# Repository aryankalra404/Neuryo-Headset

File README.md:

# Neuryo Headset

Interactive 3D models of the Neuryo EEG + heart-rate headset. Each design is its own model; the start page lists them and lets you switch between them.

**Open it:** https://aryankalra404.github.io/Neuryo-Headset/

| Design | What it is | Direct link |
|---|---|---|
| v1 · 26 Oct design | 4 channels: AF7, AF8, Fz, Pz. TP9 + TP10 linked reference, Fpz ground, saline sponge pods, forehead heart sensor. Has AR and try-on. | https://aryankalra404.github.io/Neuryo-Headset/designs/v1/ |
| v2 · 29 Oct research plan | 6 channels: Fp1, Fp2, Fz, Pz, TP10, eye (VEOG). TP9 reference alone, Fpz bias, hydrogel on the forehead, semi-dry pods in hair, earlobe heart-sensor clip. Built from the Neuryo-Research library (decisions D01 to D28) on the shared realistic head. Superseded by v3. | https://aryankalra404.github.io/Neuryo-Headset/designs/v2/ |
| v3 · 29 Oct review | Superseded by v4. 6 channels on the head (Fp1, Fp2, Fz, Pz, M2, eye) on an 8-channel ADS1299 at gain 12. M1 mastoid-bone reference on SRB2, Fpz bias. One 4 mm snap socket per site with swappable inserts: paste on the forehead, semi-dry pods in hair. **Test kit** toggle adds ECG on channel 7 and dry comparison inserts; **Confidence** colours each part by how sure the plan is. | https://aryankalra404.github.io/Neuryo-Headset/designs/v3/ |
| v4 · 7 Nov product design | Superseded by v6, which keeps its midline band and carriages. Was the launch design (v4.4). A 5-minute in-clinic recording at baseline, day 7 and every visit of a depression treatment course. 7 channels on the head (Fp1, Fp2, Fz, Cz, Pz, M2, eye), M1 reference, Fpz bias. Single-use 3-pad hydrogel forehead strip placed by a nasion template, earlobe heart clip, BMI270, 1000 mAh at the back. Buildable frame for 500–580 mm circumference and 300–390 mm nasion–inion: bought hard-hat ratchet harness with a 3 mm lining or a 7 mm small-head insert; midline band 3D-printed already in the head's curve (PA12, PETG for fit tests) with a TPU tail through a cam lock; spring-loaded semi-dry pods pinned at one size number (1–9) read off a size tape; damp single-use foam tips (2–3 mm proud, set weight) topped up only when the app's wetting check asks; wipe-clean silicone lining. Main board (v4.5): about 70 × 50 mm in the brow module, the analog half copied from the open Low-Cost-EEG board plus a Seeed XIAO ESP32-S3. Page adds a 9-step **Session walkthrough**, head-size and nasion–inion sliders, a buy/print parts list and frame build steps, and a **Single-use vs reusable** overlay. | https://aryankalra404.github.io/Neuryo-Headset/designs/v4/ |
| v5 · arch concept (v5.2) | Superseded by v6. Same electronics and sites as v4.5, new frame: spring arch over Cz, main board in a pod above the left ear and battery above the right, temple arms to soft pads, rear band with a hook under the occiput and a dial. v5.2 (8 Nov): Fz, Cz and Pz in spring carriages on a rigid spine clipped to the arch at Cz, one soft spring per pod. Forehead bare apart from the strip. | https://aryankalra404.github.io/Neuryo-Headset/designs/v5/ |
| v6 · 8 Nov head ring + v4 midline | Superseded by v7 (kept for comparison, as the adjustable-Fz alternative). v4's midline band lying on the head with a spring carriage per pod (one size number 1–9 sets Fz and Pz from Fpz), held between a small front anchor (about 34 × 34 × 7.5 mm, replacing v4's brow module) and a cam lock above the rear dial. Head ring: a front band across the forehead above the strip and v5's rear band with a hook under the occiput and a dial. Board in a pod above the left ear, battery above the right. Real windows in the band and real lead slots in the carriages. v6.1 (9 Nov): the real rev B board from KiCad (77 × 50 mm), pods resized to about 98 × 77 × 22 mm. v6.2 (10 Nov): carriages wrap the rails and click into size notches, rails 3 mm thick beside the windows, Cz pod moved to the test kit (6 channels on the product headset). v6.3 (11 Nov): no Cz in the product or the test kit (decision D36); the band has Fz and Pz windows only, with two lead clips on the solid section between them, and a corrected size table. | https://aryankalra404.github.io/Neuryo-Headset/designs/v6/ |
| v7.2 · 11 Nov simplified ring and fixed Fz | Lead design (proposed; nothing printed or measured). From the 11 Nov design review of v6.3; same montage, electrodes, rev B board and firmware. One continuous printed head ring strap from a pivot behind the left pod, across the forehead and under both pods (a tunnel in each pod's base, 2 × M3); the PN521 nape section kept whole and pivoting on its ends, so the pods carry no ring tension. Chin-strap tabs on the ring (strap in the test kit). Side pods with a flat, chamfered face parallel to the board, 15.5 mm off the skin (was 22), JP1 and TP1 left off; outer box about 107.0 × 69.1 × 25.7 mm, headset 180.4 mm wide (v6.3: 189.1). A clip-in **nasion gauge** sets the midline band's zero; the forehead strip goes on after the headset, from the anchor's pointer. Fz fixed at 69 mm behind the zero (up to 9 mm from its 10-20 site, the same spot every visit); only Pz has a size setting. Tail travel corrected to about 81 mm, pull tab with stretch marks, spare end folded in half under two keepers. v7.1 (same day): fixes from the review of v7, dark grey leads with colour end bands, and a **Midline module** toggle showing the forehead-only configuration (an option, not decided). v7.2 (same day): the hair pod reworked as one printed body with a fill tube and an Ag/AgCl pin standing in the foam, guided in its carriage by two pins that stop it and show the force; print files for the pod in `designs/v7/stl/`. | https://aryankalra404.github.io/Neuryo-Headset/designs/v7/ |
| Ultracortex pod adapter · 8 Nov | Test rig part: holds a Neuryo pod in an OpenBCI Ultracortex Mark IV frame node at Fz, Cz or Pz to test a rigid frame with a spring per pod. Four STL print files plus the generator `tools/uc_adapter.py`. | https://aryankalra404.github.io/Neuryo-Headset/designs/uc-adapter/ |

Add `#v1` to `#v7` to the start page link to open a design straight away.

**Docs:** [docs/](docs/README.md): one file per design ([v1](docs/v1.md), [v2](docs/v2.md), [v3](docs/v3.md), [v4](docs/v4.md), [v5](docs/v5.md), [v6](docs/v6.md), [v7](docs/v7.md), each with why it changed from the one before) and the [shared head](docs/head.md) with all 77 measured 10-10 positions plus the mastoid points M1/M2.

**PCB:** [pcb/](pcb/README.md): rev B in KiCad 10 (77 × 50 mm: Low-Cost-EEG's analog half + a XIAO ESP32-S3, final pin map, ERC/DRC/netlist checks, firmware) and the Low-Cost-EEG reference design it copies (Altium project, Gerbers, schematic, report; GPL-3.0). 5th pass, 11 Nov (every assembled part has an LCSC number, R37 10 k, J1 drill 0.8 mm, JLCPCB placement file, clean order folder, firmware USB-restart fix); 4th pass, 10 Nov (series resistors on SPI, I²C pull-ups, D10 to RESET, test pads, plated XIAO battery holes, bench build). Laid out, waiting for review, not ordered. Rev A (30 Oct, made for v3) is in the git history.

## Adding a new design
1. Copy the latest design folder, for example `designs/v5/` to `designs/v6/`, and change the model in `designs/v6/index.html`. It already loads the shared head from `designs/shared/head/`; pick electrode sites by name (`HEAD.sites.F3`, `HEAD.extra.M1` and so on, see [docs/head.md](docs/head.md)).
2. Add an entry to `designs/designs.json` with its `id`, `name`, `date`, `path`, `channels`, `summary` and `status`.
3. Add `docs/v6.md` with its spec and what changed from v5, and why.

The new design then shows up on the start page and in the switcher.

## Using it on Meta Quest 3S (v1)
1. Open https://aryankalra404.github.io/Neuryo-Headset/designs/v1/ in the **Meta Quest Browser**.
2. Tap **View in AR** and allow the permission prompt.
3. Pinch the headset to lift it off the mannequin, or pinch an electrode pod to pull it out on its own. Pinch empty space to move everything. Reset on the panel puts parts back.
   Right stick: explode. Left stick: turn and resize. Use the floating panel for Inside, Electronics only, Labels and Head.

AR is tested on v1 only. v3 and v4 show a **View in AR** button on headsets that support WebXR, but it has not been tested on the Quest yet. Try-on is v1 only.

## Try it on (webcam or phone)
v7: https://aryankalra404.github.io/Neuryo-Headset/designs/v7/tryon.html (or **Try it on** on the v7 page). v6: https://aryankalra404.github.io/Neuryo-Headset/designs/v6/tryon.html. v1: the link below.

### v1
Open https://aryankalra404.github.io/Neuryo-Headset/tryon.html on a laptop or phone, press **Start camera** and face the camera. The headset locks onto your head at true size. Use Size / Up-down / Forward-back to fit it, **Show head guide** to check the fit, and **Take photo** to save a picture. Face tracking runs in the browser with Google MediaPipe; the video is not uploaded.

## In a normal browser
Rotate and zoom the model, see inside, open the **Electrode build** and **Board guide** walkthroughs, and check sources under **Details → Sources**.

v3 adds a Product / Test kit mode switch, a **Display** menu, **Copy link** (opens exactly what you are looking at), **Measure**, and two new Details tabs: **Build** (parts list, wiring, tests) and **Changes** (what moved since v2 and why). See [docs/v3.md](docs/v3.md#on-the-page).

v4 adds **Fit & finish** (head circumference 500–580 mm and nasion–inion 300–390 mm sliders that give the ratchet setting and lining, the strip height and the band size number 1–9; silicone lining vs the dropped knit idea; lining and shell colours), a **Session walkthrough** under Guides (G), a **Session** tab, **Channel numbers** (N) and a **Single-use vs reusable** overlay (U). See [docs/v4.md](docs/v4.md#on-the-page).

v1 is built from the 26 Oct design doc. v2 is built from the 29 Oct research plan; its module, board layout and battery are carried over from v1. Shapes and sizes neither source gives are marked as model estimates in the page. In v2, **All sites** shows every measured 10-10 position on the head.

## Shared head
`designs/shared/head/` holds the mannequin every design uses (v1 to v7): MakeHuman base mesh (CC0), 540 mm head circumference, sites measured with the 10-20 rules. The scripts in `tools/` rebuild it; see [docs/head.md](docs/head.md).

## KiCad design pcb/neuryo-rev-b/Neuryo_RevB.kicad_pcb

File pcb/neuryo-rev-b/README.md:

# Neuryo rev B (KiCad 10)

The Low-Cost-EEG board (commit `3730d31`) with its ESP32-S3 module side replaced by a Seeed XIAO ESP32-S3, the review changes from `../README.md`, I²C headers for the earlobe MAX30102 and a BMI270, and a 77 × 50 mm outline for the v6 left pod. Battery and switch sit at the right-hand (digital) end. The stack-up is JLCPCB 4-layer 1.6 mm. 4th pass (10 Nov): 330 Ω on SCLK/MOSI/CS, I²C pull-ups, D10 → RESET, test pads, plated XIAO battery holes, bench firmware build. 5th pass (11 Nov): part numbers for everything JLCPCB assembles, R37 10 k, J1 drill 0.8 mm, order folder in [review/order-draft-do-not-order/](review/order-draft-do-not-order/). **Not ordered; waiting for review.**

| Path | What it is |
|---|---|
| `Neuryo_RevB.kicad_pro` / `.kicad_sch` / `.kicad_pcb` / `.kicad_dru` | The rev B project (KiCad 10.0.8). Zones are filled. |
| `Neuryo_RevB.pretty`, `Neuryo_RevB.kicad_sym` | New footprints and symbols: Seeed XIAO-ESP32-S3-SMD (from Seeed's library), KiCad's SOT-23 and SW_SPDT_PCM12 (C&K PCM12 slide switch), 1×4 header, 2N7002, PWR_FLAG |
| `Low_Cost_EEG-import-fps.pretty` | Footprints imported from the reference |
| [CHANGES.md](CHANGES.md) | Every change, why, its source, and whether it is verified |
| [REVIEW-CHECKLIST.md](REVIEW-CHECKLIST.md) | What to check before ordering |
| [ASSEMBLY.md](ASSEMBLY.md) | Hand-soldered parts (XIAO through its battery holes), bench board, battery polarity, electrodes |
| [firmware/](firmware/) | Rev B firmware (PlatformIO, XIAO ESP32-S3): upstream's with rev B pins, SRB2, command-driven RESET/START, USB interlock, battery and I²C status |
| `baseline-import/` | The reference imported into KiCad unchanged (plus the translated Altium clearance rules), for side-by-side comparison |
| `review/` | Renders (`top.png`, `bottom.png`), `schematic.pdf`, `layers.pdf`, ERC/DRC JSON, netlists, the netlist and copper diffs, the baseline's reports, a draft fab set (not for ordering) and `bom-jlc.csv`, the BOM with part numbers to order from |
| `scripts/` | The scripts that made every edit: `edit_sch.py`, `edit_pcb.py`, `edit_pcb2.py`, `silkplace.py` (reference-designator placement), `convmod.py` (KiCad 5 footprint to current format), `edit_sch_mpn.py` (restores the reference's part numbers), `jlcbom.py` (BOM with part numbers, no KiCad needed), `edit_sch4.py` and `edit_pcb4.py` (4th pass, one letter per plan step), `edit_sch5.py` and `edit_pcb5.py` (5th pass), `jlcbom.py` / `jlccpl.py` (BOM and placement file), plus the checks (`netdiff.py`, `copperdiff.py`, `drcsum.py`, `gerbdiff.py`) and `runner.sh`, which runs `kicad-cli` and PlatformIO. The paths inside them are the build machine's. |

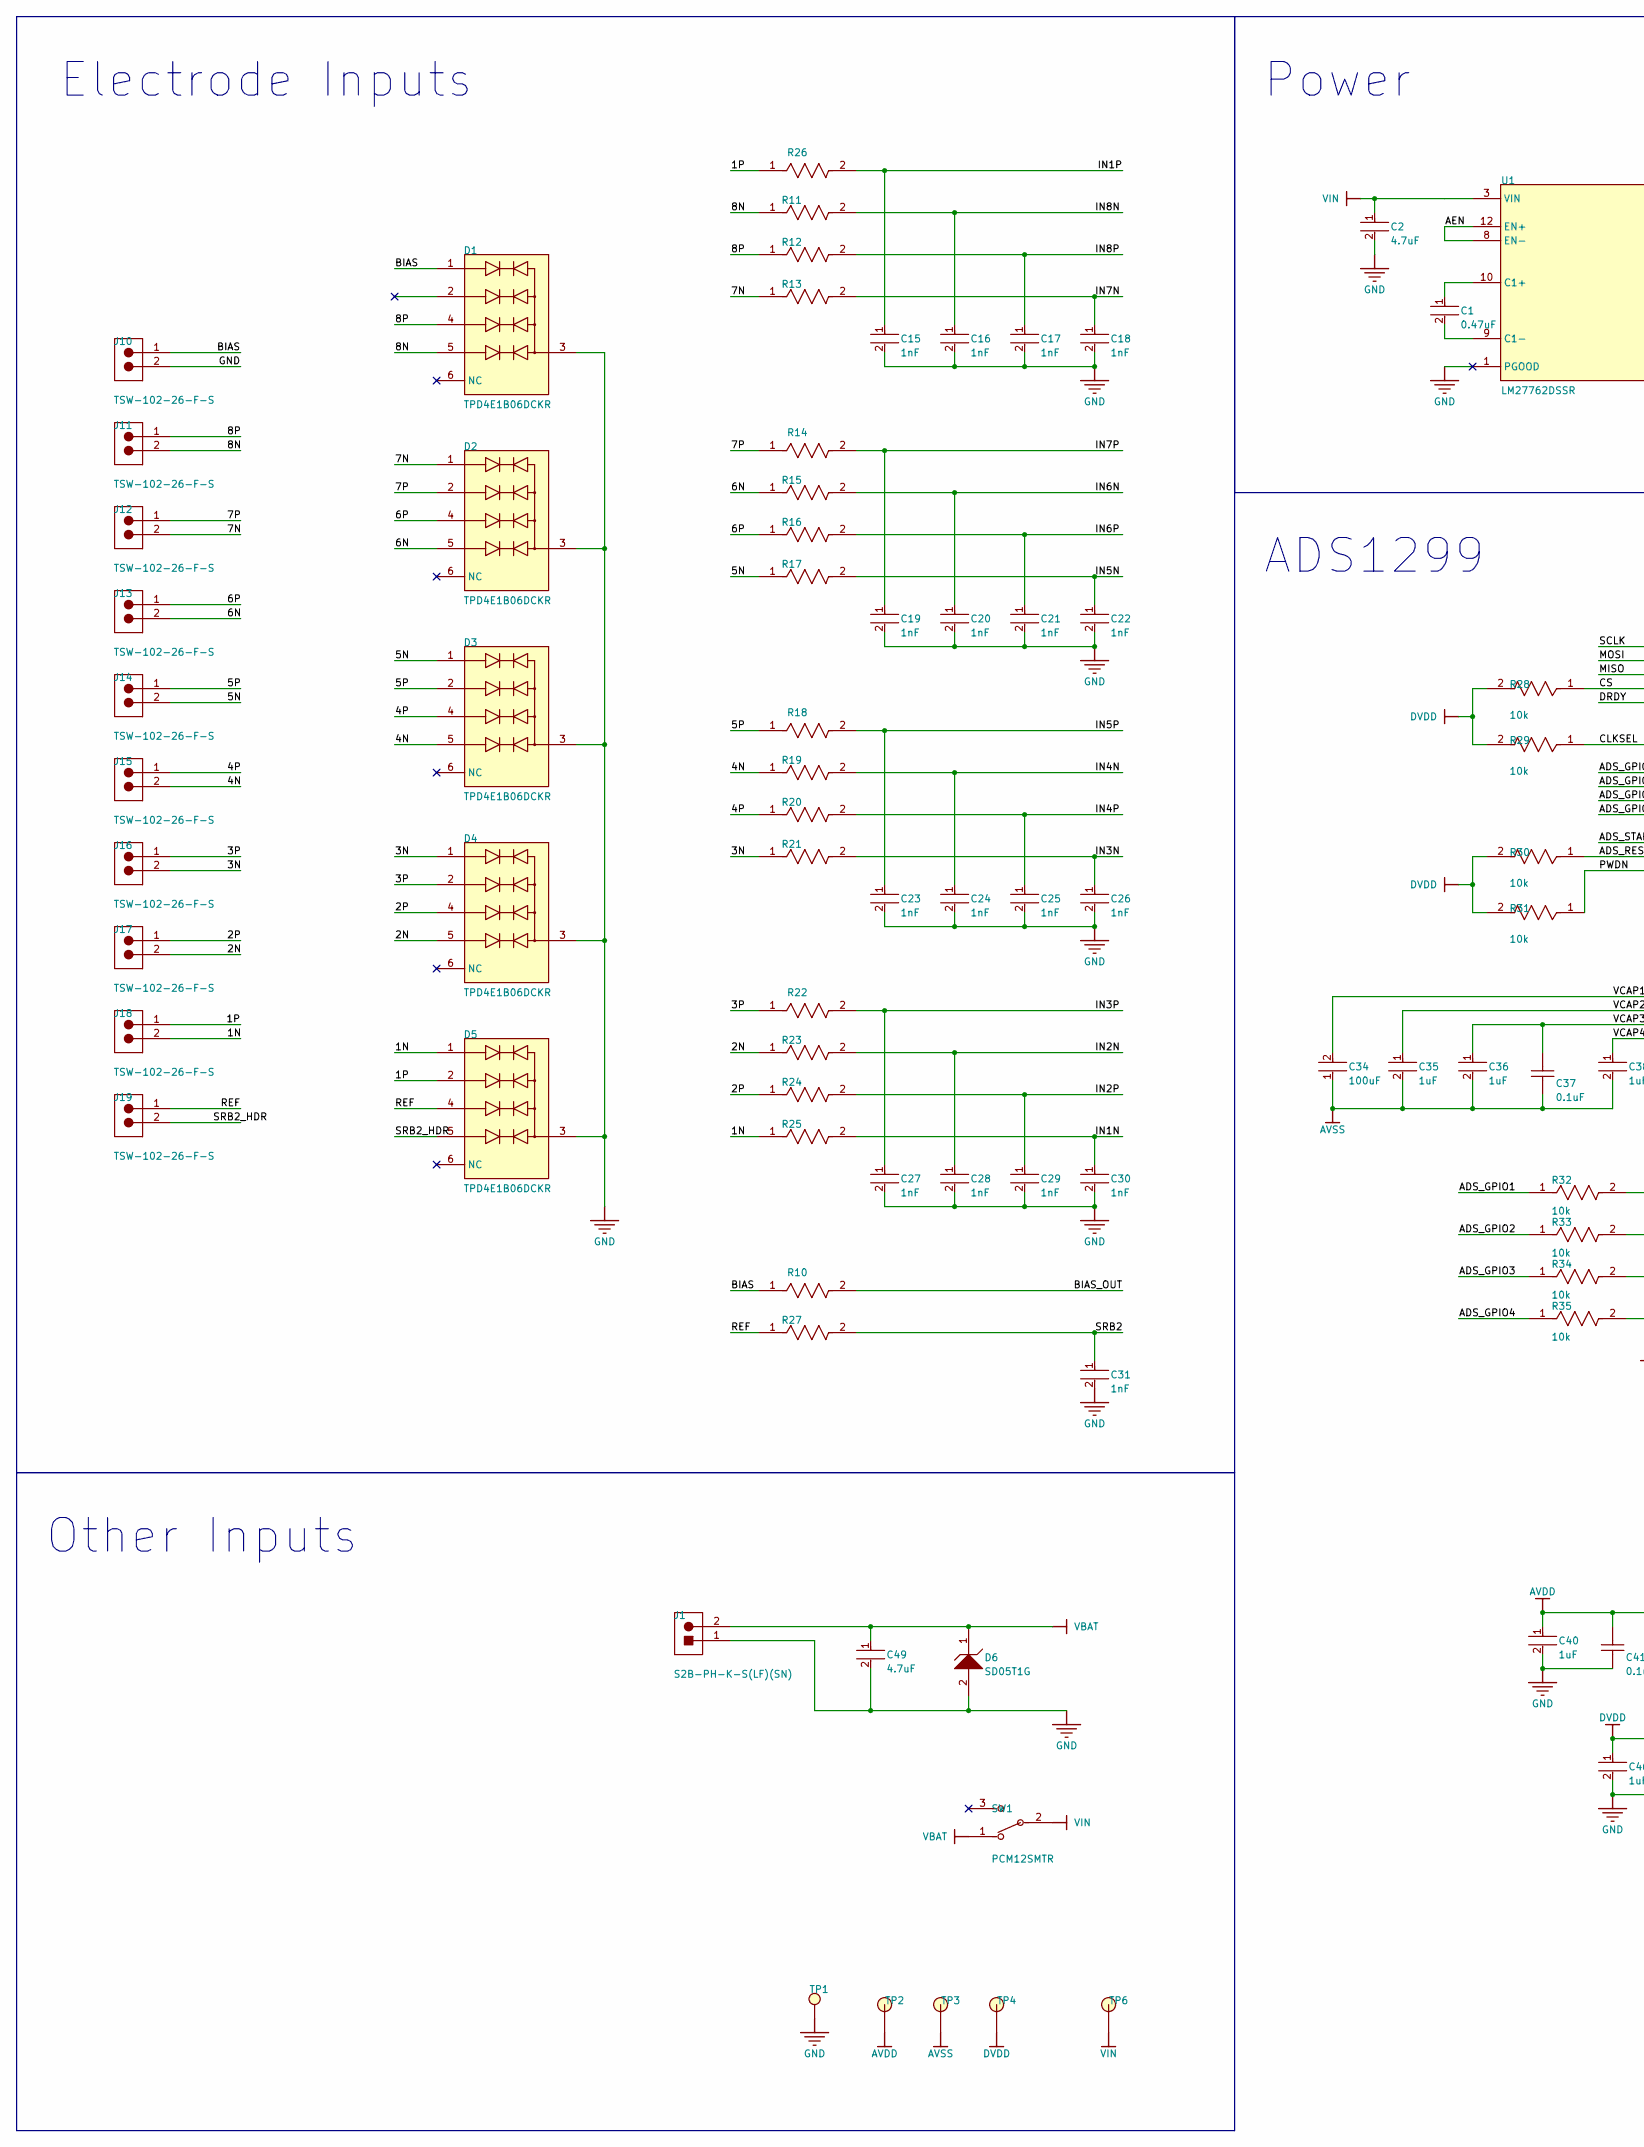
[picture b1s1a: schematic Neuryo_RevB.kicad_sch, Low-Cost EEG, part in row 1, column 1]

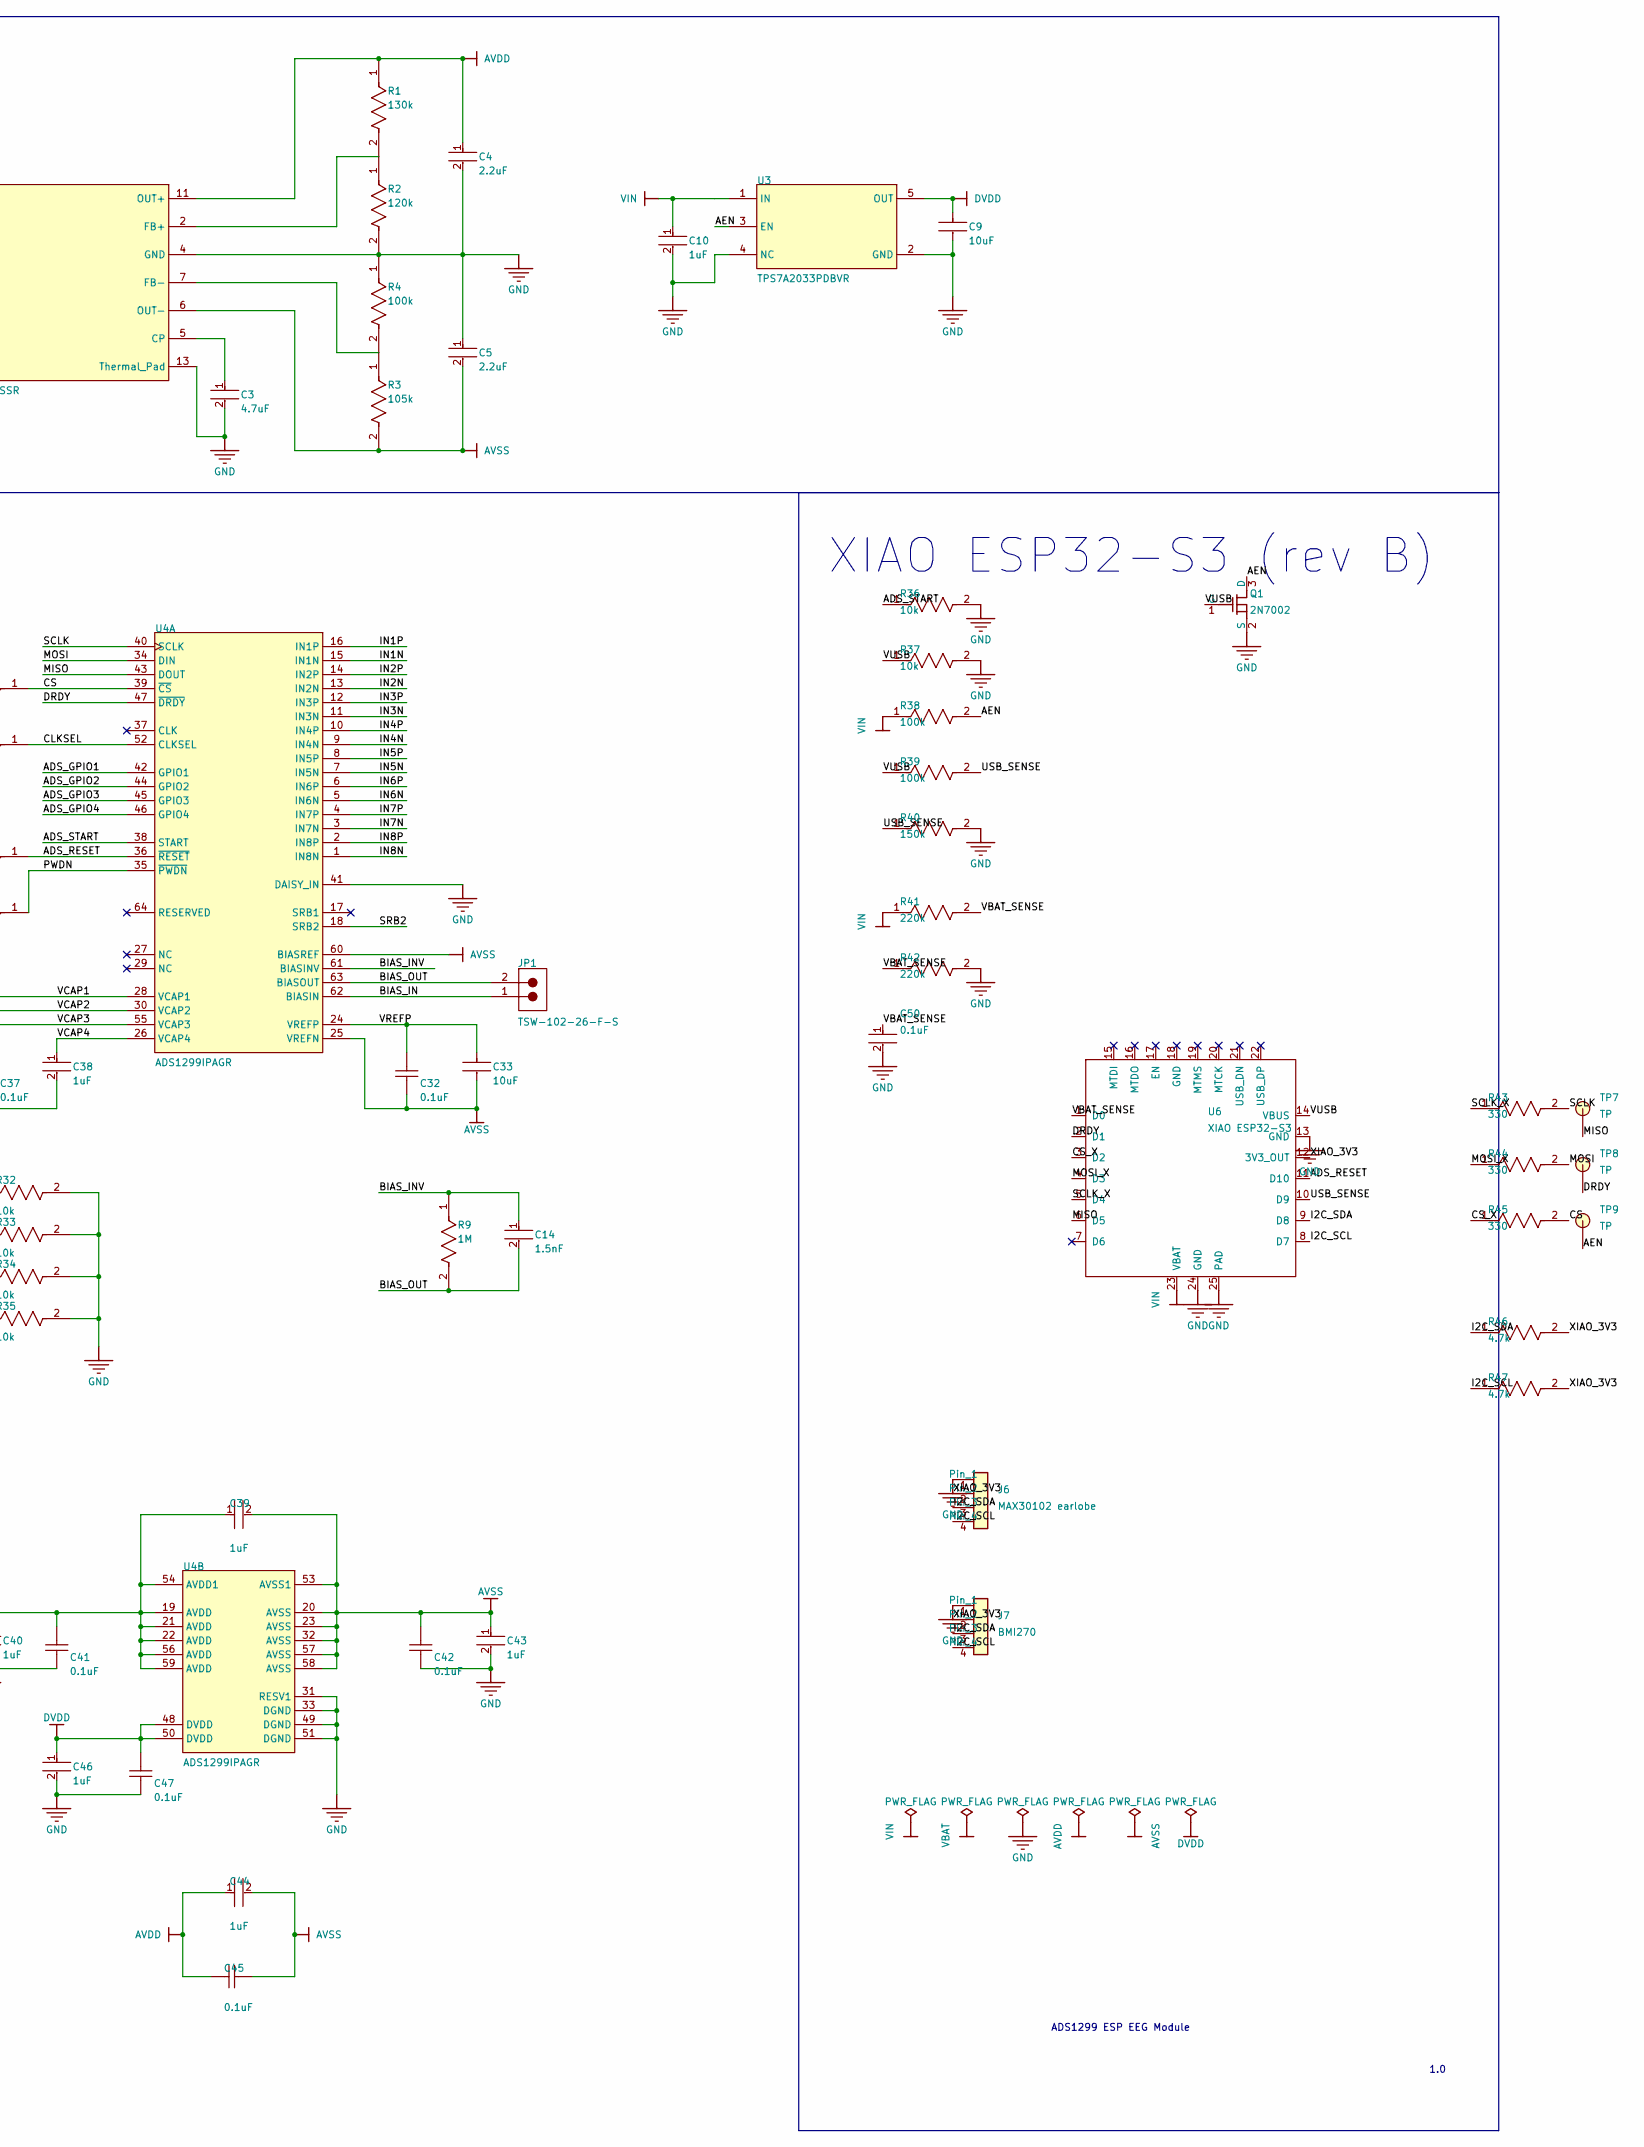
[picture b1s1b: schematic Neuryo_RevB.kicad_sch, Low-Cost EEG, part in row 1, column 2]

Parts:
C1: 0.47uF; FP-C0603C-CF-MFG; VOLTAGE RATING 16 V; TOLERANCE 0.1; MPN KEMET C0603C474K4RACAUTO; DIGIKEY DESCRIPTION Cap Ceramic 0.47uF 16V X7R 10% Pad SMD 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
C2, C3, C49: 4.7uF; FP-GCJ21B-0_3-IPC_A; TOLERANCE 10%; VOLTAGE RATING (DC) 16V; MPN Samsung CL21B475KOFNNNE; LCSC C107365
C4, C5: 2.2uF; FP-GCM21B-0_15-IPC_B; VOLTAGE RATING (DC) 16V; TOLERANCE 10%; MPN Murata GCM21BR71C225KA64K; LCSC C1852484
C9, C33: 10uF; FP-GRJ21B-0_3-0_2-MFG; MPN Samsung CL21A106KAYNNNE; LCSC C15850
C10, C35, C36, C38, C39, C40, C43, C44, C46: 1uF; FP-CC0603-DA-MFG; TOLERANCE 0.1; VOLTAGE 16 V; MPN Yageo CC0603KRX7R7BB105; DIGIKEY DESCRIPTION CAP CER 1UF 16V X7R 0603
C14: 1.5nF; FP-C0603C-CF-MFG; VOLTAGE RATING 100 V; TOLERANCE 0.05; MPN Murata GRM1885C1H152JA01D; DIGIKEY DESCRIPTION CAP CER 1500PF 100V NP0 0603
C15, C16, C17, C18, C19, C20, C21, C22, C23, C24, C25, C26, C27, C28, C29, C30, C31: 1nF; FP-C0603C-CF-MFG; VOLTAGE RATING 50 V; TOLERANCE 0.01; MPN Murata GRM1885C1H102FA01D; DIGIKEY DESCRIPTION CAP CER 1000PF 50V 1% NP0 0603
C32, C37, C41, C42, C45, C47: 0.1uF; CAPC1608X87X45LL20T05; MPN KEMET C0603C104J4RACTU; LCSC C22401913
C34: 100uF; FP-GRM31C-0_3-e0_3_0_8-IPC_B; MPN Murata GRM31CR61A107MEA8L; LCSC C883598
C50: 0.1uF; FP-C0603C-CF-MFG; MPN YAGEO CC0603KRX7R9BB104; LCSC C14663
D1, D2, D3, D4, D5: TPD4E1B06DCKR; TVS_TPD4E1B06DCKR; MPN Texas Instruments TPD4E1B06DCKR; LCSC C840093
D6: SD05T1G; ONSC-SOD-323-2-477-02_G_V; MPN onsemi SD05T1G; LCSC C233423
J1: S2B-PH-K-S(LF)(SN); JST-S2B-PH-K-S_V; TOLERANCE 20%; VOLTAGE RATING (DC) 50 V; MPN JST S2B-PH-K-S(LF)(SN)
J6: MAX30102 earlobe; PinHeader_1x04_P2.54_TSW; MPN Samtec TSW-104-07-T-S or leads soldered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
J7: BMI270; PinHeader_1x04_P2.54_TSW; MPN Samtec TSW-104-07-T-S or leads soldered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
J10, J11, J12, J13, J14, J15, J16, J17, J18, J19: TSW-102-26-F-S; SMTC-TSW-102-26-XX-S; MPN Samtec TSW-102-26-F-S
JP1: TSW-102-26-F-S; SMTC-TSW-102-26-XX-S; MPN Samtec TSW-102-26-F-S
Q1: 2N7002; SOT-23; MPN Nexperia 2N7002,215; LCSC C65189
R1: 130k; FP-MCT0603-IPC_B; VOLTAGE RATING (DC) 50V; TOLERANCE 0.1%; MPN Yageo RT0603BRD07130KL; LCSC C861109
R2: 120k; FP-RT0603-MFG; TOLERANCE 0.001; VOLTAGE RATING 75V; MPN Yageo RT0603BRD07120KL; MOUSER DESCRIPTION Thin Film Resistors - SMD 1/10W 120K oh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
R3: 105k; FP-RT0603-MFG; POWER RATING 0.1W; VOLTAGE RATING 75V; MPN Yageo RT0603BRD07105KL; MOUSER DESCRIPTION Thin Film Resistors 1/10W 105K ohm .1% 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
R4: 100k; FP-AT0603-IPC_A; RATINGS AEC-Q200; TOLERANCE 0.1%; MPN Yageo AT0603BRD07100KL; LCSC C855559
R9: 1M; FP-MCT0603-MFG; TOLERANCE 1%; MPN UNI-ROYAL 0603WAF1004T5E; LCSC C22935
R10: 51k; FP-MCT0603-IPC_A; TOLERANCE 0.1%; MPN Yageo RT0603BRD0751KL; LCSC C861458
R11, R12, R13, R14, R15, R16, R17, R18, R19, R20, R21, R22, R23, R24, R25, R26, R27: 2.2k; FP-MCT0603-IPC_A; TOLERANCE 0.1%; MPN Yageo RT0603BRD072K2L; LCSC C861295
R28, R29, R30, R31, R32, R33, R34, R35, R36, R37: 10k; FP-AC0603-MFG; MPN UNI-ROYAL 0603WAF1002T5E; LCSC C25804
R38, R39: 100k; FP-AC0603-MFG; MPN UNI-ROYAL 0603WAF1003T5E; LCSC C25803
R40: 150k; FP-AC0603-MFG; MPN UNI-ROYAL 0603WAF1503T5E; LCSC C22807
R41, R42: 220k; FP-AC0603-MFG; MPN UNI-ROYAL 0603WAF2203T5E; LCSC C22961
R43, R44, R45: 330; FP-AC0603-MFG; MPN UNI-ROYAL 0603WAF3300T5E; LCSC C23138
R46, R47: 4.7k; FP-AC0603-MFG; MPN UNI-ROYAL 0603WAF4701T5E; LCSC C23162
SW1: PCM12SMTR; SW_SPDT_PCM12; MPN C&K PCM12SMTR; LCSC C221841
TP1: KSTN-5003; FORWARD VOLTAGE 1.08 V; MPN Keystone 5003
TP2, TP3, TP4, TP6: TP; TP_SMD_2mm
TP7, TP8, TP9: TP; TP_SMD_D1.0; MPN (copper test pad, not assembled)
U1: LM27762DSSR; FP-DSS0012B-MFG; MPN Texas Instruments LM27762DSSR; LCSC C473398
U3: TPS7A2033PDBVR; FP-DBV0005A-MFG; MPN Texas Instruments TPS7A2033PDBVR; LCSC C2862740
U4: ADS1299IPAGR; PAG0064A_M; MPN Texas Instruments ADS1299IPAGR; LCSC C476817
U6: XIAO ESP32-S3; XIAO-ESP32-S3-SMD; MPN Seeed Studio XIAO ESP32-S3 (113991114)

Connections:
1N: D5.1 (IO1), J18.2, R25.1
1P: D5.2 (IO2), J18.1, R26.1
2N: D4.5 (IO4), J17.2, R23.1
2P: D4.4 (IO3), J17.1, R24.1
3N: D4.1 (IO1), J16.2, R21.1
3P: D4.2 (IO2), J16.1, R22.1
4N: D3.5 (IO4), J15.2, R19.1
4P: D3.4 (IO3), J15.1, R20.1
5N: D3.1 (IO1), J14.2, R17.1
5P: D3.2 (IO2), J14.1, R18.1
6N: D2.5 (IO4), J13.2, R15.1
6P: D2.4 (IO3), J13.1, R16.1
7N: D2.1 (IO1), J12.2, R13.1
7P: D2.2 (IO2), J12.1, R14.1
8N: D1.5 (IO4), J11.2, R11.1
8P: D1.4 (IO3), J11.1, R12.1
ADS_GPIO1: R32.1, U4.42 (GPIO1)
ADS_GPIO2: R33.1, U4.44 (GPIO2)
ADS_GPIO3: R34.1, U4.45 (GPIO3)
ADS_GPIO4: R35.1, U4.46 (GPIO4)
ADS_RESET: R30.1, U4.36 (~RESET), U6.11 (D10)
ADS_START: R36.1, U4.38 (START)
AEN: Q1.3 (D), R38.2, TP9.1, U1.8 (EN-), U1.12 (EN+), U3.3 (EN)
AVDD: C4.1, C39.1, C40.1, C41.2, C44.1, C45.2, R1.1, TP2.1, U1.11 (OUT+), U4.19 (AVDD), U4.21 (AVDD), U4.22 (AVDD), U4.54 (AVDD1), U4.56 (AVDD), U4.59 (AVDD)
AVSS: C5.2, C32.1, C33.2, C34.1, C35.2, C36.2, C37.1, C38.2, C39.2, C42.2, C43.1, C44.2, C45.1, R3.2, TP3.1, U1.6 (OUT-), U4.20 (AVSS), U4.23 (AVSS), U4.25 (VREFN), U4.32 (AVSS), U4.53 (AVSS1), U4.57 (AVSS), U4.58 (AVSS), U4.60 (BIASREF)
BIAS: D1.1 (IO1), J10.1, R10.1
BIAS_IN: JP1.1, U4.62 (BIASIN)
BIAS_INV: C14.1, R9.1, U4.61 (BIASINV)
BIAS_OUT: C14.2, JP1.2, R9.2, R10.2, U4.63 (BIASOUT)
CLKSEL: R29.1, U4.52 (CLKSEL)
CS: R28.1, R45.2, U4.39 (~CS)
CS_X: R45.1, U6.3 (D2)
DRDY: TP8.1, U4.47 (~DRDY), U6.2 (D1)
DVDD: C9.1, C46.1, C47.2, R28.2, R29.2, R30.2, R31.2, TP4.1, U3.5 (OUT), U4.48 (DVDD), U4.50 (DVDD)
GND: C2.2, C3.2, C4.2, C5.1, C9.2, C10.2, C15.2, C16.2, C17.2, C18.2, C19.2, C20.2, C21.2, C22.2, C23.2, C24.2, C25.2, C26.2, C27.2, C28.2, C29.2, C30.2, C31.2, C40.2, C41.1, C42.1, C43.2, C46.2, C47.1, C49.2, C50.2, D1.3 (GND), D2.3 (GND), D3.3 (GND), D4.3 (GND), D5.3 (GND), D6.2 (A), J1.1, J6.1, J7.1, J10.2, Q1.2 (S), R2.2, R4.1, R32.2, R33.2, R34.2, R35.2, R36.2, R37.2, R40.2, R42.2, TP1.1, U1.1 (PGOOD), U1.4 (GND), U1.13 (Thermal_Pad), U3.2 (GND), U3.4 (NC), U4.31 (RESV1), U4.33 (DGND), U4.41 (DAISY_IN), U4.49 (DGND), U4.51 (DGND), U6.13 (GND), U6.24 (GND), U6.25 (PAD)
I2C_SCL: J6.4, J7.4, R47.1, U6.8 (D7)
I2C_SDA: J6.3, J7.3, R46.1, U6.9 (D8)
IN1N: C30.1, R25.2, U4.15 (IN1N)
IN1P: C15.1, R26.2, U4.16 (IN1P)
IN2N: C28.1, R23.2, U4.13 (IN2N)
IN2P: C29.1, R24.2, U4.14 (IN2P)
IN3N: C26.1, R21.2, U4.11 (IN3N)
IN3P: C27.1, R22.2, U4.12 (IN3P)
IN4N: C24.1, R19.2, U4.9 (IN4N)
IN4P: C25.1, R20.2, U4.10 (IN4P)
IN5N: C22.1, R17.2, U4.7 (IN5N)
IN5P: C23.1, R18.2, U4.8 (IN5P)
IN6N: C20.1, R15.2, U4.5 (IN6N)
IN6P: C21.1, R16.2, U4.6 (IN6P)
IN7N: C18.1, R13.2, U4.3 (IN7N)
IN7P: C19.1, R14.2, U4.4 (IN7P)
IN8N: C16.1, R11.2, U4.1 (IN8N)
IN8P: C17.1, R12.2, U4.2 (IN8P)
MISO: TP7.1, U4.43 (DOUT), U6.6 (D5)
MOSI: R44.2, U4.34 (DIN)
MOSI_X: R44.1, U6.4 (D3)
NetC1_1: C1.1, U1.10 (C1+)
NetC1_2: C1.2, U1.9 (C1-)
NetC3_1: C3.1, U1.5 (CP)
NetR1_2: R1.2, R2.1, U1.2 (FB+)
NetR3_1: R3.1, R4.2, U1.7 (FB-)
PWDN: R31.1, U4.35 (~PWDN)
REF: D5.4 (IO3), J19.1, R27.1
SCLK: R43.2, U4.40 (SCLK)
SCLK_X: R43.1, U6.5 (D4)
SRB2: C31.1, R27.2, U4.18 (SRB2)
SRB2_HDR: D5.5 (IO4), J19.2
USB_SENSE: R39.2, R40.1, U6.10 (D9)
VBAT: C49.1, D6.1 (K), J1.2, SW1.1
VBAT_SENSE: C50.1, R41.2, R42.1, U6.1 (D0)
VCAP1: C34.2, U4.28 (VCAP1)
VCAP2: C35.1, U4.30 (VCAP2)
VCAP3: C36.1, C37.2, U4.55 (VCAP3)
VCAP4: C38.1, U4.26 (VCAP4)
VIN: C2.1, C10.1, R38.1, R41.1, SW1.2 (COMM), TP6.1, U1.3 (VIN), U3.1 (IN), U6.23 (VBAT)
VREFP: C32.2, C33.1, U4.24 (VREFP)
VUSB: Q1.1 (G), R37.1, R39.1, U6.14 (VBUS)
XIAO_3V3: J6.2, J7.2, R46.2, R47.2, U6.12 (3V3_OUT)

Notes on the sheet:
XIAO ESP32-S3 (rev B)
Electrode Inputs
ADS1299 ESP EEG Module
Other Inputs
ADS1299
${REVISION}
Power

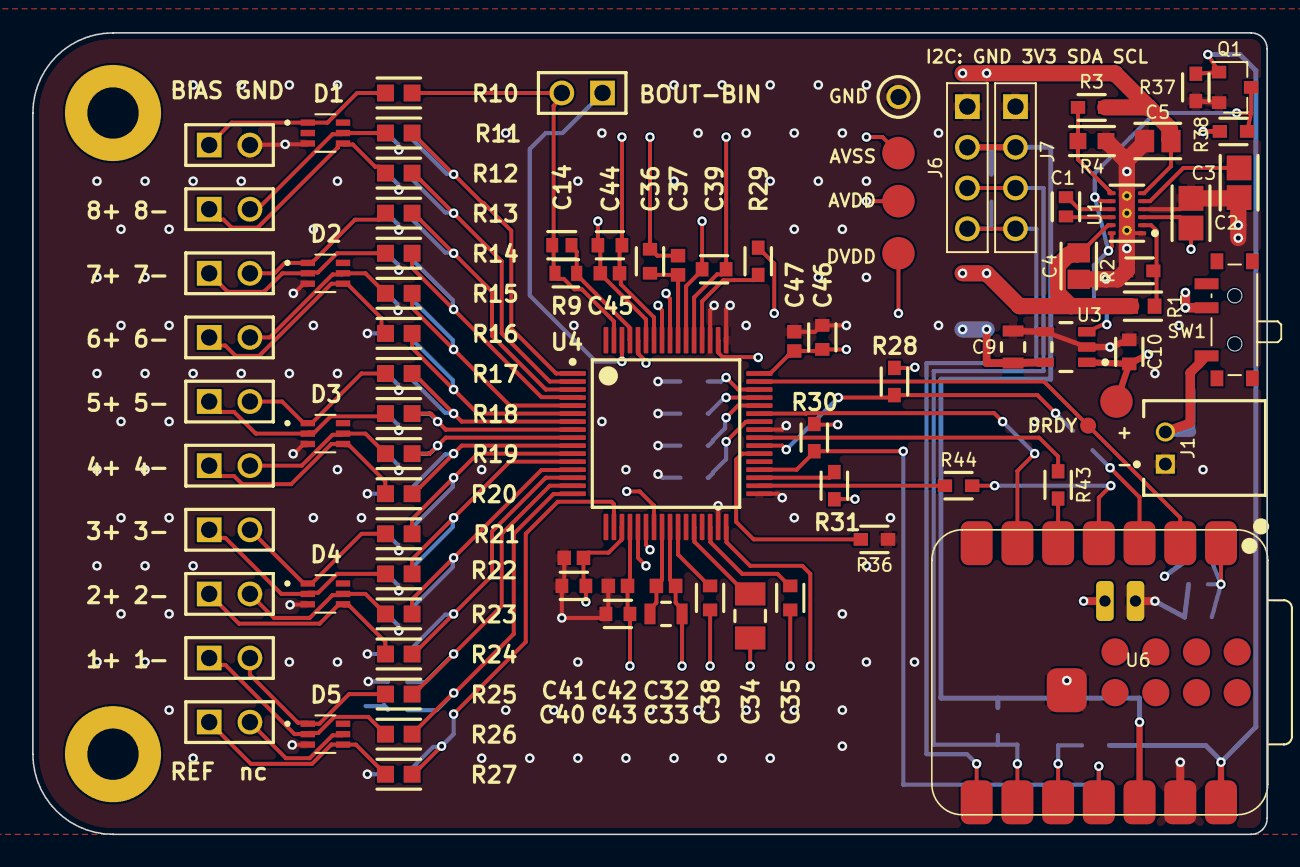
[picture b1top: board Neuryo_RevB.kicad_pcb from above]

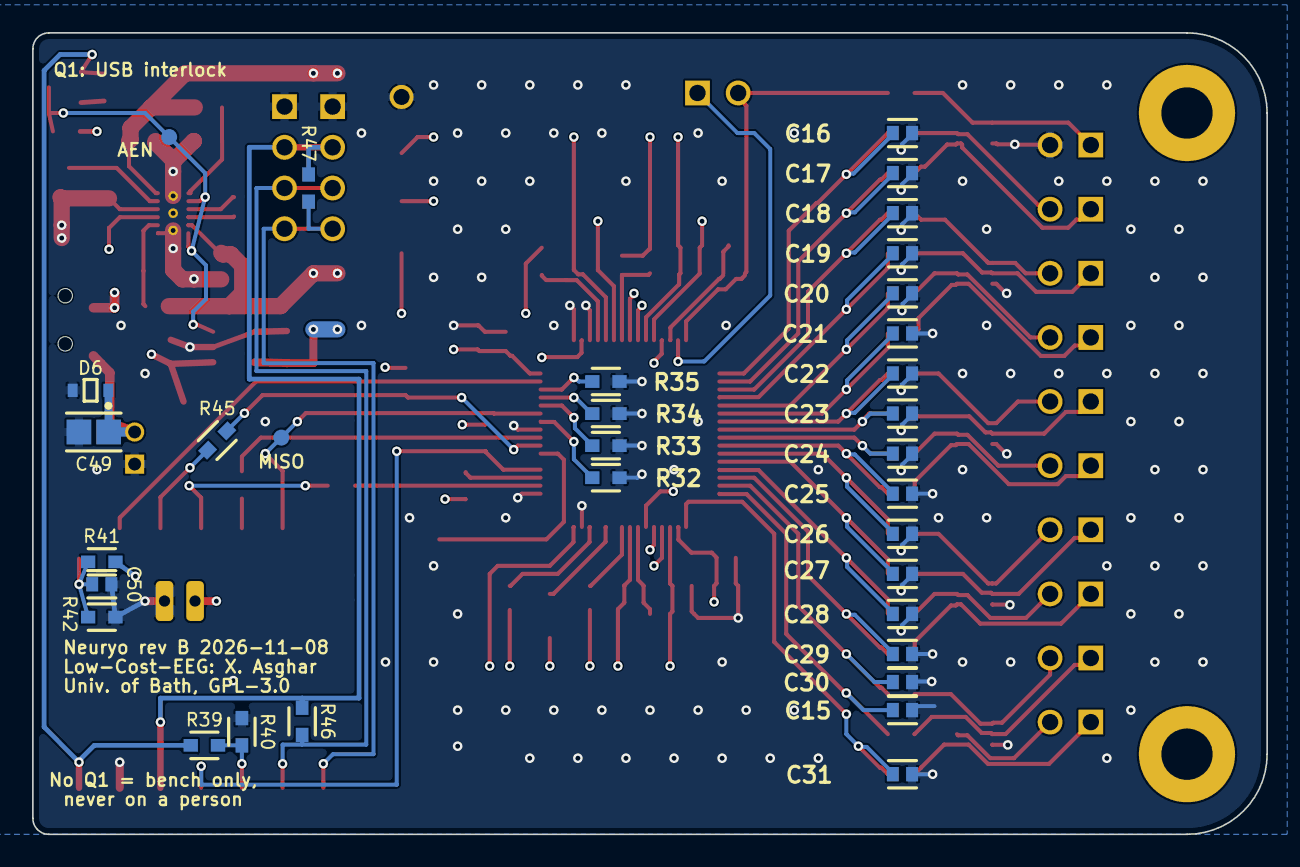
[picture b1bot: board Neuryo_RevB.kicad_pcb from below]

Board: 4 copper layers, 77.0 x 50.0 mm, 120 parts (33 on the bottom side), 78 nets.

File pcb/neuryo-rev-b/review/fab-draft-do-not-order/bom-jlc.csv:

Comment,Designator,Footprint,Quantity,MPN,LCSC Part #,Note
0.47uF,C1,FP-C0603C-CF-MFG,1,Yageo C0603C474K4RACAUTO,,
4.7uF,"C2, C3, C49",FP-GCJ21B-0_3-IPC_A,3,Murata GCJ21BR71C475KA01K,,
2.2uF,"C4, C5",FP-GCM21B-0_15-IPC_B,2,Murata GCM21BR71C225KA64K,,
10uF,"C9, C33",FP-GRJ21B-0_3-0_2-MFG,2,Murata GRJ21BR61E106KE01L,,
1uF,"C10, C35, C36, C38, C39, C40, C43, C44, C46",FP-CC0603-DA-MFG,9,Yageo CC0603KRX7R7BB105,,
1.5nF,C14,FP-C0603C-CF-MFG,1,Murata GRM1885C2A152JA01D,,
1nF,"C15, C16, C17, C18, C19, C20, C21, C22, C23, C24, C25, C26, C27, C28, C29, C30, C31",FP-C0603C-CF-MFG,17,Yageo C0603C102F5GACTU,,
0.1uF,"C32, C37, C41, C42, C45, C47",CAPC1608X87X45LL20T05,6,Yageo C0603X104J4RACTU,,
100uF,C34,FP-GRM31C-0_3-e0_3_0_8-IPC_B,1,Murata GRM31CR61A107MEA8L,,
0.1uF,C50,FP-C0603C-CF-MFG,1,YAGEO CC0603KRX7R9BB104,C14663,
TPD4E1B06DCKR,"D1, D2, D3, D4, D5",TVS_TPD4E1B06DCKR,5,Texas Instruments TPD4E1B06DCKR,C840093,
SD05T1G,D6,ONSC-SOD-323-2-477-02_G_V,1,onsemi SD05T1G,,
2N7002,Q1,SOT-23,1,"Nexperia 2N7002,215",C65189,
130k,R1,FP-MCT0603-IPC_B,1,Vishay MCT06030D1303BP100,,
120k,R2,FP-RT0603-MFG,1,Yageo RT0603BRD07120KL,,
105k,R3,FP-RT0603-MFG,1,Yageo RT0603BRD07105KL,,
100k,R4,FP-AT0603-IPC_A,1,Yageo AT0603BRD07100KL,,
1M,R9,FP-MCT0603-MFG,1,Vishay MCT06030C1004FPW00,,
51k,R10,FP-MCT0603-IPC_A,1,Vishay MCT06030D5102BP500,,
2.2k,"R11, R12, R13, R14, R15, R16, R17, R18, R19, R20, R21, R22, R23, R24, R25, R26, R27",FP-MCT0603-IPC_A,17,Vishay MCT06030D2201BP500,,
10k,"R28, R29, R30, R31, R32, R33, R34, R35",FP-AC0603-MFG,8,UNI-ROYAL 0603WAF1002T5E,C25804,JLCPCB Basic equivalent (10k 1% 0603 thick film) of the reference Yageo AC0603FR-7W10KL
10k,R36,FP-AC0603-MFG,1,UNI-ROYAL 0603WAF1002T5E,C25804,
100k,"R37, R38, R39",FP-AC0603-MFG,3,UNI-ROYAL 0603WAF1003T5E,C25803,
150k,R40,FP-AC0603-MFG,1,UNI-ROYAL 0603WAF1503T5E,C22807,
220k,"R41, R42",FP-AC0603-MFG,2,UNI-ROYAL 0603WAF2203T5E,C22961,
330,"R43, R44, R45",FP-AC0603-MFG,3,UNI-ROYAL 0603WAF3300T5E,C23138,
4.7k,"R46, R47",FP-AC0603-MFG,2,UNI-ROYAL 0603WAF4701T5E,C23162,
PCM12SMTR,SW1,SW_SPDT_PCM12,1,C&K PCM12SMTR,C221841,
LM27762DSSR,U1,FP-DSS0012B-MFG,1,Texas Instruments LM27762DSSR,C473398,
TPS7A2033PDBVR,U3,FP-DBV0005A-MFG,1,Texas Instruments TPS7A2033PDBVR,C2862740,
ADS1299IPAGR,U4,PAG0064A_M,1,Texas Instruments ADS1299IPAGR,C476817,

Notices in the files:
pcb/neuryo-rev-b/firmware/src/main.cpp:
Based on the Low-Cost-EEG firmware (X. Asghar, GPL-3.0, upstream commit 3730d31,
Software/Firmware_Platformio_Project/src/main.cpp). BLE service, characteristic, packet format (28 bytes:
counter + 3 status + 8 x 3 channel bytes) and batching (8 packets per notify) are unchanged.
pcb/README.md:
Licence:
The reference is GPL-3.0, so rev B's board files will be GPL-3.0 too. That is fine for the prototype; decide before the product whether to keep the board open or redraw it.
pcb/kicad/neuryo.kicad_pcb:
Derived from OpenBCI Cyton (CC BY-SA 4.0)
